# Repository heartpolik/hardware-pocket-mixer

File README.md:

# diy-mixer

Портативний 4-канальний стереомікшер для поля й столу. У репозиторії два підпроєкти:

| Тека | Що це | Стан |
|---|---|---|
| [analog-mixer/](analog-mixer/README.md) | **Rev A, аналоговий**: звук іде крізь фейдери й op-amp, ±12 V від 2S LiPo, ESP32-C3 керує ключами й метрами; дві плати | плати розведено, Gerber і BOM готові |
| [digital-mixer/](digital-mixer/README.md) | **Цифровий**, формфактор і функції на зразок TX-6: АЦП → Teensy 4.1 (мікс, EQ, ефекти) → ЦАП, USB-аудіоінтерфейс 8 каналів, MIDI, рекордер на microSD | плата 4 шари розведена (DRC 0), Gerber / BOM — далі |
| [common/](common/README.md) | спільні скрипти: схема, розстановка, трасування, footprint, 3D | — |

Правила роботи для обох — [CLAUDE.md](CLAUDE.md). Рішення кожного підпроєкту — у його
`docs/decisions.md`.

## Походження та ліцензія

Source location: <https://github.com/heartpolik/hardware-pocket-mixer>.

| Тека | Ліцензія | Чому |
|---|---|---|
| [analog-mixer/](analog-mixer/README.md#походження-та-ліцензія), [common/](common/README.md) | CERN-OHL-S-2.0+ ([LICENSE](LICENSE)) | Rev A похідний від **mixerli** (Stahl, 2023): <https://github.com/stahlnow/mixerli> |
| [digital-mixer/](digital-mixer/README.md#ліцензія) | GPL-3.0-or-later ([digital-mixer/LICENSE](digital-mixer/LICENSE)) | власна розробка, файлів mixerli немає (DM36) |

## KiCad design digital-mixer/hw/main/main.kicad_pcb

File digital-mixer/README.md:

# digital-mixer

Портативний цифровий стереомікшер з USB-аудіоінтерфейсом. Від teenage engineering TX-6 беремо
формфактор і функції (EQ, компресор, ефекти, cue, сцени, MIDI, рекордер), але не схемотехніку.

> [!NOTE]
> Стан: плата розведена ([docs/04-pcb.md](docs/04-pcb.md)), прошивка 0.2 з емулятором ([docs/06-firmware.md](docs/06-firmware.md)), схема — [docs/03-schematic.md](docs/03-schematic.md); ТЗ — [docs/01-spec.md](docs/01-spec.md), дослідження — [docs/00-research.md](docs/00-research.md). Наступний крок — макет на готових
> платах: Teensy 4.1 + PCM1865 + PCM5102A, перевірка USB-аудіо 8 каналів у Windows, macOS та iOS.

```mermaid
flowchart LR
    IN(["4 стерео входи"]) --> ADC["2 × PCM1865<br/>TDM"] --> T["Teensy 4.1<br/>мікс, EQ, компресор,<br/>2 FX-шини, метри"]
    T --> DAC["3 × PCM5102A"] --> OUT(["MAIN, AUX,<br/>навушники"])
    T <-->|"USB HS: 8 вх / 2 вих,<br/>MIDI"| PC(["DAW"])
    T --> SD[("microSD<br/>рекордер")]
    UI["Фейдери, 12 енкодерів,<br/>кнопки, дисплей 1,47″"] <--> T
```

| Документ | Зміст |
|---|---|
| [docs/00-research.md](docs/00-research.md) | TX-6, варіанти архітектури, канали й USB, живлення, функції, ризики |
| [docs/01-spec.md](docs/01-spec.md) | **ТЗ Rev 1:** функціонал, керування, роз'єми, ТТХ |
| [docs/02-components.md](docs/02-components.md) | Фейдери, енкодери, живлення 1S, монтаж Teensy, AliExpress чи JLCPCB |
| [docs/03-schematic.md](docs/03-schematic.md) | **Принципова схема** (KiCad, [PDF](hw/main/main.pdf)), виводи Teensy, макет розташування |
| [docs/04-pcb.md](docs/04-pcb.md) | **Плата:** чотиришарова 104,5 × 136,5 мм (компоновка C), Teensy на гребінках з PSRAM (DM35), розведена, DRC 0 порушень, 0 розривів |
| [docs/05-fab.md](docs/05-fab.md) | **Виготовлення:** Gerber, BOM, файли PCBA для NextPCB, [інтерактивний BOM](docs/ibom/ibom.html), порядок ручного монтажу |
| [docs/07-review.md](docs/07-review.md) | **Перевірка перед замовленням:** що знайдено й виправлено, що перевірено, що звірити; покращення до наступної версії |
| [docs/06-firmware.md](docs/06-firmware.md) | **Прошивка й емулятор:** ядро C++ ([firmware/](firmware/README.md)), емулятор на SDL2, керування, ефекти, MIDI CC, що перевірити на макеті |
| [docs/calc/](docs/calc/power.py) | Розрахунок живлення |
| [docs/decisions.md](docs/decisions.md) | Журнал рішень цифрового підпроєкту (DM1…) |
| [docs/datasheets/](docs/datasheets/README.md) | Datasheets цього підпроєкту |

З аналогового [Rev A](../analog-mixer/README.md) переносимо деталі там, де вони підходять:
USB-C GCT USB4085, захист USBLC6-2SC6, MBR0530 і AO3401A (load sharing).

## Ліцензія

SPDX-License-Identifier: GPL-3.0-or-later — повний текст у [LICENSE](LICENSE). Стосується всього в
`digital-mixer/`: схеми, плати, бібліотек, документації й прошивки (DM36).

Цифрова версія не є похідною від mixerli: файлів звідти в ній немає (джеки — PJ-327A, footprint і модель
згенеровано тут за кресленням продавця, DM38). Чужі файли зберігають свої ліцензії:
символ Teensy 4.1 від XenGi — MIT ([hw/lib/third_party](hw/lib/third_party/LICENSE-teensy_library.txt));
стандартні бібліотеки KiCad — за їхньою ліцензією з винятком для проєктів; datasheets — власність
виробників.

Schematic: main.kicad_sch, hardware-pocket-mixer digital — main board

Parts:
C1, C2, C4, C5, C6, C7, C20, C23, C32, C35, C42, C44, C53, C55, C64, C66, C82: 10u; C_1206_3216Metric
C3, C17, C19, C21, C22, C29, C31, C33, C34, C38, C39, C40, C43, C49, C50, C51, C54, C60, C61, C62, C65, C75, C76, C77, C78, C79, C80, C81: 100n; C_0805_2012Metric
C8, C9: 22u; C_1206_3216Metric
C10, C16, C28, C69, C70, C73, C74: 1u; C_0805_2012Metric
C11: 2.2u; C_1206_3216Metric
C12, C13, C14, C15, C24, C25, C26, C27: 10u 16V; CP_Elec_4x5.4
C18, C30, C41, C52, C63: 1u; C_1206_3216Metric
C36, C37, C47, C48, C58, C59, C71, C72: 2.2u; C_0805_2012Metric
C45, C46, C56, C57, C67, C68: 2.2n; C_0805_2012Metric
D1: red; LED_0805_2012Metric
D2: green; LED_0805_2012Metric
D3: MBR0530; D_SOD-123
DS1: GMT147SPI 1.47in 172x320; LCD_GMT147SPI
J1: GCT USB4110-GF-A; USB_C_Receptacle_GCT_USB4110
J2: LiPo 1S 3000 mAh (з платою захисту); JST_PH_S2B-PH-SM4-TB_1x02-1MP_P2.00mm_Horizontal
J3: IN1 PJ-327A; Jack_3.5mm_PJ-327A_SMT_Horizontal
J4: IN2 PJ-327A; Jack_3.5mm_PJ-327A_SMT_Horizontal
J5: IN3 PJ-327A; Jack_3.5mm_PJ-327A_SMT_Horizontal
J6: IN4 PJ-327A; Jack_3.5mm_PJ-327A_SMT_Horizontal
J7: MAIN OUT PJ-327A; Jack_3.5mm_PJ-327A_SMT_Horizontal
J8: AUX OUT PJ-327A; Jack_3.5mm_PJ-327A_SMT_Horizontal
J9: PHONES PJ-327A; Jack_3.5mm_PJ-327A_SMT_Horizontal
J10: MIDI OUT PJ-327A; Jack_3.5mm_PJ-327A_SMT_Horizontal
L1: 0.47u XFL4015-471ME; L_Coilcraft_XFL4015
Q1: AO3401A; SOT-23
R1, R2, R3, R4: 4.7k; R_0805_2012Metric
R5, R6, R7, R8, R9, R31, R40: 33; R_0805_2012Metric
R10, R11, R24, R26, R28, R30, R33, R35, R37, R39: 10k; R_0805_2012Metric
R12, R13, R19, R22, R23, R25, R27, R29, R32, R34, R36, R38: 100k; R_0805_2012Metric
R14, R15: 5.1k; R_0805_2012Metric
R16: 2.4k; R_0805_2012Metric
R17, R18: 1k; R_0805_2012Metric
R20: 665k; R_0805_2012Metric
R21: 91k; R_0805_2012Metric
R41, R42, R43, R44, R45, R46: 470; R_0805_2012Metric
R47: 33 0.5W; R_2010_5025Metric
R48: 10 0.25W; R_1206_3216Metric
RV1, RV2, RV3, RV4: RS201111J011 10k B; Potentiometer_Alps_RS20111_Single_Slide
SW1: Power 5.8mm DPDT self-lock SMD; SW_Push_Latching_DPDT_5.8mm_SMD
SW2: EC12SY ch1.1; RotaryEncoder_EC12SY_SMD
SW3: EC12SY ch1.2; RotaryEncoder_EC12SY_SMD
SW4: EC12SY ch1.3; RotaryEncoder_EC12SY_SMD
SW5: Mute 1 TSF-1266; SW_TSF-1266_6x6mm_SMD
SW6: EC12SY ch2.1; RotaryEncoder_EC12SY_SMD
SW7: EC12SY ch2.2; RotaryEncoder_EC12SY_SMD
SW8: EC12SY ch2.3; RotaryEncoder_EC12SY_SMD
SW9: Mute 2 TSF-1266; SW_TSF-1266_6x6mm_SMD
SW10: EC12SY ch3.1; RotaryEncoder_EC12SY_SMD
SW11: EC12SY ch3.2; RotaryEncoder_EC12SY_SMD
SW12: EC12SY ch3.3; RotaryEncoder_EC12SY_SMD
SW13: Mute 3 TSF-1266; SW_TSF-1266_6x6mm_SMD
SW14: EC12SY ch4.1; RotaryEncoder_EC12SY_SMD
SW15: EC12SY ch4.2; RotaryEncoder_EC12SY_SMD
SW16: EC12SY ch4.3; RotaryEncoder_EC12SY_SMD
SW17: Mute 4 TSF-1266; SW_TSF-1266_6x6mm_SMD
SW18: EC12SY master; RotaryEncoder_EC12SY_SMD
SW19: FX1 TSF-1266; SW_TSF-1266_6x6mm_SMD
SW20: FX2 TSF-1266; SW_TSF-1266_6x6mm_SMD
SW21: AUX TSF-1266; SW_TSF-1266_6x6mm_SMD
SW22: SHIFT TSF-1266; SW_TSF-1266_6x6mm_SMD
U1: Teensy 4.1; Teensy41_THT
U2: USBLC6-2SC6; SOT-23-6
U3: TP4056; SOIC-8-1EP_3.9x4.9mm_P1.27mm_EP2.41x3.3mm
U4: TPS63802; Texas_VSON-HR-10_2x3mm_P0.5mm
U5: LP5907MFX-3.3; SOT-23-5
U6, U7: PCM1865; TSSOP-30_4.4x7.8mm_P0.5mm
U8, U9, U10: PCM5102A; TSSOP-20_4.4x6.5mm_P0.65mm
U11: TPA6132A2; WQFN-16-1EP_3x3mm_P0.5mm_EP1.6x1.6mm
U12, U13, U14: MCP23017-E/SO; SOIC-28W_7.5x17.9mm_P1.27mm

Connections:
/+3V3: C2.1, C21.1, C22.1, C23.1, C33.1, C34.1, C35.1, C40.1, C42.1, C51.1, C53.1, C62.1, C64.1, C75.1, C76.1, C77.1, C82.1, DS1.2, R1.1, R2.1, R3.1, R4.1, R47.1, RV1.3, RV2.3, RV3.3, RV4.3, U1.15 (3V3), U1.46 (3V3), U1.51 (3V3), U6.13 (DVDD), U6.14 (IOVDD), U7.13 (DVDD), U7.14 (IOVDD), U7.25 (MS/AD), U8.20 (DVDD), U9.20 (DVDD), U10.20 (DVDD), U12.9 (V_{DD}), U12.18 (~RESET), U13.9 (V_{DD}), U13.15 (A0), U13.18 (~RESET), U14.9 (V_{DD}), U14.16 (A1), U14.18 (~RESET)
/+3V3A: C11.1, C17.1, C18.1, C29.1, C30.1, C38.1, C39.1, C41.1, C49.1, C50.1, C52.1, C60.1, C61.1, C63.1, U5.5 (OUT), U6.8 (AVDD), U7.8 (AVDD), U8.1 (CPVDD), U8.8 (AVDD), U9.1 (CPVDD), U9.8 (AVDD), U10.1 (CPVDD), U10.8 (AVDD)
/+4V2: C1.1, C8.1, C9.1, C10.1, C71.1, R20.1, U1.48 (VIN), U4.6 (VOUT), U5.1 (IN), U5.3 (EN), U11.14 (VDD)
/ADC1_DOUT: R31.1, U6.18 (DOUT)
/ADC1_IN1_L: C12.1, U6.3 (VINL1/VIN1P)
/ADC1_IN1_R: C13.1, U6.4 (VINR1/VIN2P)
/ADC1_IN2_L: C14.1, U6.1 (VINL2/VIN1M)
/ADC1_IN2_R: C15.1, U6.2 (VINR2/VIN2M)
/ADC1_LDO: C19.1, C20.1, U6.11 (LDO)
/ADC1_VREF: C16.1, U6.6 (VREF)
/ADC2_DOUT: R40.1, U7.18 (DOUT)
/ADC2_IN3_L: C24.1, U7.3 (VINL1/VIN1P)
/ADC2_IN3_R: C25.1, U7.4 (VINR1/VIN2P)
/ADC2_IN4_L: C26.1, U7.1 (VINL2/VIN1M)
/ADC2_IN4_R: C27.1, U7.2 (VINR2/VIN2M)
/ADC2_LDO: C31.1, C32.1, U7.11 (LDO)
/ADC2_VREF: C28.1, U7.6 (VREF)
/ADC_BCK: R7.2, U6.17 (BCK), U7.17 (BCK)
/ADC_BCK_T: R7.1, U1.6 (4_BCLK2)
/ADC_DOUT: R31.2, R40.2, U1.7 (5_IN2)
/ADC_LRCK: R8.2, U6.16 (LRCK), U7.16 (LRCK)
/ADC_LRCK_T: R8.1, U1.5 (3_LRCLK2)
/ADC_MCLK: R9.2, U6.15 (SCKI), U7.15 (SCKI)
/ADC_MCLK_T: R9.1, U1.25 (33_MCLK2)
/AUX_CAPM: C47.2, U9.4 (CAPM)
/AUX_CAPP: C47.1, U9.2 (CAPP)
/AUX_L: C56.1, J8.4 (T), R43.2
/AUX_LDOO: C54.1, C55.1, U9.18 (LDOO)
/AUX_OL: R43.1, U9.6 (OUTL)
/AUX_OR: R44.1, U9.7 (OUTR)
/AUX_R: C57.1, J8.3 (R), R44.2
/AUX_VNEG: C48.1, U9.5 (VNEG)
/BAT+: C5.1, J2.1, Q1.3 (D), U3.5 (BAT)
/BB_FB: R20.2, R21.1, U4.4 (FB)
/BB_L1: L1.1, U4.9 (L1)
/BB_L2: L1.2, U4.7 (L2)
/BTN_AUX: SW21.1, U14.27 (GPA6)
/BTN_FX1: SW19.1, U14.28 (GPA7)
/BTN_FX2: SW20.1, U14.7 (GPB6)
/BTN_SHIFT: SW22.1, U1.21 (29_TX7)
/CC1: J1.A5 (CC1), R14.1
/CC2: J1.B5 (CC2), R15.1
/CHG_LED_G: D2.1 (K), U3.6 (~STDBY)
/CHG_LED_GA: D2.2 (A), R18.2
/CHG_LED_R: D1.1 (K), U3.7 (~CHRG)
/CHG_LED_RA: D1.2 (A), R17.2
/CHG_PROG: R16.1, U3.2 (PROG)
/CUE_CAPM: C58.2, U10.4 (CAPM)
/CUE_CAPP: C58.1, U10.2 (CAPP)
/CUE_L: C67.1, C69.1, R45.2
/CUE_LDOO: C65.1, C66.1, U10.18 (LDOO)
/CUE_OL: R45.1, U10.6 (OUTL)
/CUE_OR: R46.1, U10.7 (OUTR)
/CUE_R: C68.1, C70.1, R46.2
/CUE_VNEG: C59.1, U10.5 (VNEG)
/DAC_AUX: U1.24 (32_OUT1B), U9.14 (DIN)
/DAC_BCK: R5.2, U8.13 (BCK), U9.13 (BCK), U10.13 (BCK)
/DAC_BCK_T: R5.1, U1.43 (21_A7_RX5_BCLK1)
/DAC_CUE: U1.11 (9_OUT1C), U10.14 (DIN)
/DAC_LRCK: R6.2, U8.15 (LRCK), U9.15 (LRCK), U10.15 (LRCK)
/DAC_LRCK_T: R6.1, U1.42 (20_A6_TX5_LRCLK1)
/DAC_MAIN: U1.9 (7_RX2_OUT1A), U8.14 (DIN)
/DAC_XSMT: R10.1, U1.28 (36_CS), U8.17 (XSMT), U9.17 (XSMT), U10.17 (XSMT)
/ENC1_1_A: SW2.A, U12.21 (GPA0)
/ENC1_1_B: SW2.B, U12.22 (GPA1)
/ENC1_1_SW: SW2.S1, U14.21 (GPA0)
/ENC1_2_A: SW3.A, U12.23 (GPA2)
/ENC1_2_B: SW3.B, U12.24 (GPA3)
/ENC1_2_SW: SW3.S1, U14.22 (GPA1)
/ENC1_3_A: SW4.A, U12.25 (GPA4)
/ENC1_3_B: SW4.B, U12.26 (GPA5)
/ENC1_3_SW: SW4.S1, U14.23 (GPA2)
/ENC2_1_A: SW6.A, U12.1 (GPB0)
/ENC2_1_B: SW6.B, U12.2 (GPB1)
/ENC2_1_SW: SW6.S1, U14.24 (GPA3)
/ENC2_2_A: SW7.A, U12.3 (GPB2)
/ENC2_2_B: SW7.B, U12.4 (GPB3)
/ENC2_2_SW: SW7.S1, U14.25 (GPA4)
/ENC2_3_A: SW8.A, U12.5 (GPB4)
/ENC2_3_B: SW8.B, U12.6 (GPB5)
/ENC2_3_SW: SW8.S1, U14.26 (GPA5)
/ENC3_1_A: SW10.A, U13.21 (GPA0)
/ENC3_1_B: SW10.B, U13.22 (GPA1)
/ENC3_1_SW: SW10.S1, U14.1 (GPB0)
/ENC3_2_A: SW11.A, U13.23 (GPA2)
/ENC3_2_B: SW11.B, U13.24 (GPA3)
/ENC3_2_SW: SW11.S1, U14.2 (GPB1)
/ENC3_3_A: SW12.A, U13.25 (GPA4)
/ENC3_3_B: SW12.B, U13.26 (GPA5)
/ENC3_3_SW: SW12.S1, U14.3 (GPB2)
/ENC4_1_A: SW14.A, U13.1 (GPB0)
/ENC4_1_B: SW14.B, U13.2 (GPB1)
/ENC4_1_SW: SW14.S1, U14.4 (GPB3)
/ENC4_2_A: SW15.A, U13.3 (GPB2)
/ENC4_2_B: SW15.B, U13.4 (GPB3)
/ENC4_2_SW: SW15.S1, U14.5 (GPB4)
/ENC4_3_A: SW16.A, U13.5 (GPB4)
/ENC4_3_B: SW16.B, U13.6 (GPB5)
/ENC4_3_SW: SW16.S1, U14.6 (GPB5)
/ENC_M_A: SW18.A, U1.2 (0_RX1_CRX2_CS1)
/ENC_M_B: SW18.B, U1.3 (1_TX1_CTX2_MISO1)
/ENC_M_SW: SW18.S1, U1.4 (2_OUT2)
/FADER1: C78.1, RV1.2, U1.36 (14_A0_TX3_SPDIF_OUT)
/FADER2: C79.1, RV2.2, U1.37 (15_A1_RX3_SPDIF_IN)
/FADER3: C80.1, RV3.2, U1.38 (16_A2_RX4_SCL1)
/FADER4: C81.1, RV4.2, U1.39 (17_A3_TX4_SDA1)
/GND: C1.2, C2.2, C3.2, C4.2, C5.2, C6.2, C7.2, C8.2, C9.2, C10.2, C11.2, C16.2, C17.2, C18.2, C19.2, C20.2, C21.2, C22.2, C23.2, C28.2, C29.2, C30.2, C31.2, C32.2, C33.2, C34.2, C35.2, C37.2, C38.2, C39.2, C40.2, C41.2, C42.2, C43.2, C44.2, C45.2, C46.2, C48.2, C49.2, C50.2, C51.2, C52.2, C53.2, C54.2, C55.2, C56.2, C57.2, C59.2, C60.2, C61.2, C62.2, C63.2, C64.2, C65.2, C66.2, C67.2, C68.2, C71.2, C72.2, C73.2, C75.2, C76.2, C77.2, C78.2, C79.2, C80.2, C81.2, C82.2, DS1.1, J1.A1 (GND), J1.A12 (GND), J1.B1 (GND), J1.B12 (GND), J1.SH (SHIELD), J2.2, J2.MP (MountPin), J3.1 (S), J3.2 (S2), J4.1 (S), J4.2 (S2), J5.1 (S), J5.2 (S2), J6.1 (S), J6.2 (S2), J7.1 (S), J7.2 (S2), J8.1 (S), J8.2 (S2), J9.1 (S), J9.2 (S2), J10.1 (S), J10.2 (S2), R10.2, R11.2, R13.2, R14.2, R15.2, R16.2, R19.2, R21.2, R22.2, R23.2, R25.2, R27.2, R29.2, R32.2, R34.2, R36.2, R38.2, RV1.1, RV2.1, RV3.1, RV4.1, SW1.1 (A), SW2.C, SW2.MP, SW2.S2, SW3.C, SW3.MP, SW3.S2, SW4.C, SW4.MP, SW4.S2, SW5.2, SW6.C, SW6.MP, SW6.S2, SW7.C, SW7.MP, SW7.S2, SW8.C, SW8.MP, SW8.S2, SW9.2, SW10.C, SW10.MP, SW10.S2, SW11.C, SW11.MP, SW11.S2, SW12.C, SW12.MP, SW12.S2, SW13.2, SW14.C, SW14.MP, SW14.S2, SW15.C, SW15.MP, SW15.S2, SW16.C, SW16.MP, SW16.S2, SW17.2, SW18.C, SW18.MP, SW18.S2, SW19.2, SW20.2, SW21.2, SW22.2, U1.1 (GND), U1.34 (GND), U1.47 (GND), U1.52 (GND), U2.2 (GND), U3.1 (TEMP), U3.3 (GND), U3.9 (EPAD), U4.2 (MODE), U4.3 (AGND), U4.8 (GND), U5.2 (GND), U6.7 (AGND), U6.10 (XI), U6.12 (DGND), U6.25 (MS/AD), U6.26 (MD0), U7.7 (AGND), U7.10 (XI), U7.12 (DGND), U7.26 (MD0), U8.3 (CPGND), U8.9 (AGND), U8.10 (DEMP), U8.11 (FLT), U8.12 (SCK), U8.16 (FMT), U8.19 (DGND), U9.3 (CPGND), U9.9 (AGND), U9.10 (DEMP), U9.11 (FLT), U9.12 (SCK), U9.16 (FMT), U9.19 (DGND), U10.3 (CPGND), U10.9 (AGND), U10.10 (DEMP), U10.11 (FLT), U10.12 (SCK), U10.16 (FMT), U10.19 (DGND), U11.2 (INL+), U11.3 (INR+), U11.6 (G0), U11.7 (G1), U11.10 (PGND), U11.15 (SGND), U11.17 (EP), U12.10 (V_{SS}), U12.15 (A0), U12.16 (A1), U12.17 (A2), U13.10 (V_{SS}), U13.16 (A1), U13.17 (A2), U14.10 (V_{SS}), U14.15 (A0), U14.17 (A2); also elsewhere on the board
/HP_CPN: C74.2, U11.9 (CPN)
/HP_CPP: C74.1, U11.11 (CPP)
/HP_EN: R11.1, U1.29 (37_CS), U11.13 (EN)
/HP_HPVDD: C72.1, U11.12 (HPVDD)
/HP_HPVSS: C73.1, U11.8 (HPVSS)
/HP_INL: C69.2, U11.1 (INL-)
/HP_INR: C70.2, U11.4 (INR-)
/I2C2_SCL: R4.2, U1.16 (24_A10_TX6_SCL2), U12.12 (SCK), U13.12 (SCK), U14.12 (SCK)
/I2C2_SDA: R3.2, U1.17 (25_A11_RX6_SDA2), U12.13 (SDA), U13.13 (SDA), U14.13 (SDA)
/I2C_SCL: R2.2, U1.41 (19_A5_SCL), U6.24 (MC/SCL), U7.24 (MC/SCL)
/I2C_SDA: R1.2, U1.40 (18_A4_SDA), U6.23 (MOSI/SDA), U7.23 (MOSI/SDA)
/IN1_LS: C12.2, R24.2
/IN1_R: J3.3 (R), R25.1, R26.1
/IN1_RS: C13.2, R26.2
/IN1_T: J3.4 (T), R23.1, R24.1
/IN2_LS: C14.2, R28.2
/IN2_R: J4.3 (R), R29.1, R30.1
/IN2_RS: C15.2, R30.2
/IN2_T: J4.4 (T), R27.1, R28.1
/IN3_LS: C24.2, R33.2
/IN3_R: J5.3 (R), R34.1, R35.1
/IN3_RS: C25.2, R35.2
/IN3_T: J5.4 (T), R32.1, R33.1
/IN4_LS: C26.2, R37.2
/IN4_R: J6.3 (R), R38.1, R39.1
/IN4_RS: C27.2, R39.2
/IN4_T: J6.4 (T), R36.1, R37.1
/LCD_BLK: DS1.8, U1.20 (28_RX7)
/LCD_CS: DS1.7, U1.12 (10_CS_MQSR)
/LCD_DC: DS1.6, U1.32 (40_A16)
/LCD_MOSI: DS1.4, U1.13 (11_MOSI_CTX1)
/LCD_RES: DS1.5, U1.33 (41_A17)
/LCD_SCK: DS1.3, U1.35 (13_SCK_LED)
/MAIN_CAPM: C36.2, U8.4 (CAPM)
/MAIN_CAPP: C36.1, U8.2 (CAPP)
/MAIN_L: C45.1, J7.4 (T), R41.2
/MAIN_LDOO: C43.1, C44.1, U8.18 (LDOO)
/MAIN_OL: R41.1, U8.6 (OUTL)
/MAIN_OR: R42.1, U8.7 (OUTR)
/MAIN_R: C46.1, J7.3 (R), R42.2
/MAIN_VNEG: C37.1, U8.5 (VNEG)
/MCP1_INT: U1.22 (30_CRX3), U12.20 (INTA)
/MCP2_INT: U1.23 (31_CTX3), U13.20 (INTA)
/MCP3_INT: U1.44 (22_A8_CTX1), U14.20 (INTA)
/MIDI_SINK: J10.4 (T), R48.2
/MIDI_SRC: J10.3 (R), R47.2
/MIDI_TX: R48.1, U1.27 (35_TX8)
/MUTE1: SW5.1, U12.27 (GPA6)
/MUTE2: SW9.1, U12.7 (GPB6)
/MUTE3: SW13.1, U13.27 (GPA6)
/MUTE4: SW17.1, U13.7 (GPB6)
/PH_L: J9.4 (T), U11.16 (OUTL)
/PH_R: J9.3 (R), U11.5 (OUTR)
/PWR_EN: R22.1, SW1.2 (B), U4.1 (EN)
/USB_C_DN: J1.A7 (D-), J1.B7 (D-), U2.3 (I/O2)
/USB_C_DP: J1.A6 (D+), J1.B6 (D+), U2.1 (I/O1)
/USB_DN: U1.66 (D-), U2.4 (I/O2)
/USB_DP: U1.67 (D+), U2.6 (I/O1)
/VBAT_SENSE: C3.1, R12.2, R13.1, U1.30 (38_CS1_IN1)
/VBUS: C4.1, D3.2 (A), J1.A4 (VBUS), J1.A9 (VBUS), J1.B4 (VBUS), J1.B9 (VBUS), Q1.1 (G), R17.1, R18.1, R19.1, U1.49 (VUSB), U2.5 (VBUS), U3.4 (V_{CC}), U3.8 (CE)
/VSYS: C6.1, C7.1, D3.1 (K), Q1.2 (S), R12.1, SW1.3 (C), U4.10 (VIN)

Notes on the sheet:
Teensy 4.1 (DM4, DM12, DM35): на гребінках 2 × 24 крізь плату, зазор 2,5 мм під PSRAM; VIN = +4V2; перемичку VIN–VUSB на модулі РОЗРІЗАТИ, VUSB = VBUS з USB-C; USB device D−/D+ — отвори знизу модуля (креслення PJRC) → площадки 66/67 під ними, VUSB — дротик (49)
USB-C (GCT USB4110-GF-A, повністю SMD — під MASTER, DM25): аудіо, MIDI, заряд. CC 5,1k — пристрій-споживач; ESD USBLC6
Заряд 1S (DM11): TP4056, R_PROG 2,4k → 0,5 A; TEMP на GND — без NTC. CHRG / STDBY — світлодіоди
Load sharing (02, п. 4): від USB — через діод, акумулятор відключає P-MOSFET (затвор = VBUS)
Buck-boost TPS63802 → +4V2 (DM11). R1/R2 = 665k/91k → 4,15 V (VFB 0,5 V, табл. 10-5); L 0,47 µH XFL4015; C 10 µF вх., 2×22 µF вих. (>3,6 V). Вимикач — кнопка з фіксацією 5,8 мм на EN (DM27)
LP5907 3,3 V — аналог кодеків (+3V3A): < 6,5 µVrms, 250 mA; навантаження 128 mA (calc/power.py). Ємність на всій шині +3V3A — 0,7…10 µF (datasheet, COUT): 2,2 µF тут + 1 µF біля кожного кодека + 100 nF ≈ 8 µF
АЦП1 PCM1865 (I²C 0x94): входи IN1, IN2. Ведений TDM, слоти 1–4. Вхід: 10k послідовно (−6 dB з 10 kΩ входу) + 10 µF
АЦП2 PCM1865 (I²C 0x96): входи IN3, IN4. Ведений TDM, слоти 5–8. Вхід: 10k послідовно (−6 dB з 10 kΩ входу) + 10 µF
ЦАП MAIN PCM5102A: I²S, BCK PLL (SCK = GND), FMT/FLT/DEMP = GND; вихід 470 Ω + 2,2 nF (рис. 33). XSMT — спільний з Teensy
ЦАП AUX PCM5102A: I²S, BCK PLL (SCK = GND), FMT/FLT/DEMP = GND; вихід 470 Ω + 2,2 nF (рис. 33). XSMT — спільний з Teensy
ЦАП CUE PCM5102A: I²S, BCK PLL (SCK = GND), FMT/FLT/DEMP = GND; вихід 470 Ω + 2,2 nF (рис. 33). XSMT — спільний з Teensy
Навушники TPA6132A2 (рис. 27, несиметричний вхід): G0 = G1 = GND → −6 dB (2,1 Vrms ЦАП → ≈1 Vrms); EN від Teensy. QFN — лише при передзбиранні JLCPCB (DM7)
MIDI OUT, TRS Type A (DM20): кінчик = DIN 5 (через RC 10 Ω від UART), кільце = DIN 4 (RA 33 Ω від +3,3 V), гільза = DIN 2 / GND. Значення для 3,3 V — MIDI 1.0 Electrical Spec Update, рис. 1
MCP23017 #1 (I²C2, 0x20): енкодери каналів 1, 2 (A/B), Mute; GPx7 вільні; внутрішні підтяжки 100k, INTA/INTB дзеркальні → один INT
MCP23017 #2 (I²C2, 0x21): енкодери каналів 3, 4 (A/B), Mute; GPx7 вільні; внутрішні підтяжки 100k, INTA/INTB дзеркальні → один INT
MCP23017 #3 (I²C2, 0x22): кнопки 12 енкодерів каналів (DM28: натискання — фільтр / компресор, скидання значення) і кнопки AUX, FX I, FX II (GPA6, GPA7, GPB6) — найближчий до правої колонки; GPB7 вільний
Канал 1: 3 енкодери EC12SY SMD з кнопкою (шари EQ / посили / канал, DM6, DM26), фейдер 35 мм Alps RS201111J011 (DM8, DM39), Mute — тактова кнопка TSF-1266 (DM16)
Канал 2: 3 енкодери EC12SY SMD з кнопкою (шари EQ / посили / канал, DM6, DM26), фейдер 35 мм Alps RS201111J011 (DM8, DM39), Mute — тактова кнопка TSF-1266 (DM16)
Канал 3: 3 енкодери EC12SY SMD з кнопкою (шари EQ / посили / канал, DM6, DM26), фейдер 35 мм Alps RS201111J011 (DM8, DM39), Mute — тактова кнопка TSF-1266 (DM16)
Канал 4: 3 енкодери EC12SY SMD з кнопкою (шари EQ / посили / канал, DM6, DM26), фейдер 35 мм Alps RS201111J011 (DM8, DM39), Mute — тактова кнопка TSF-1266 (DM16)
Майстер: енкодер EC12SY з кнопкою, кнопки AUX, FX I, FX II, SHIFT (TSF-1266; CUE = SHIFT + Mute, DM28); дисплей GMT147SPI 1,47" 172×320 ST7789P3, SPI, на гребінці (DM18, DM23); виводи — за кресленням продавця
Прапорці живлення: шини, які в символах не мають «виходу живлення» (GND, вихід 3,3 V Teensy, VBUS, внутрішні LDO PCM1865, накачка TPA6132A2, VSYS після діода / ключа)

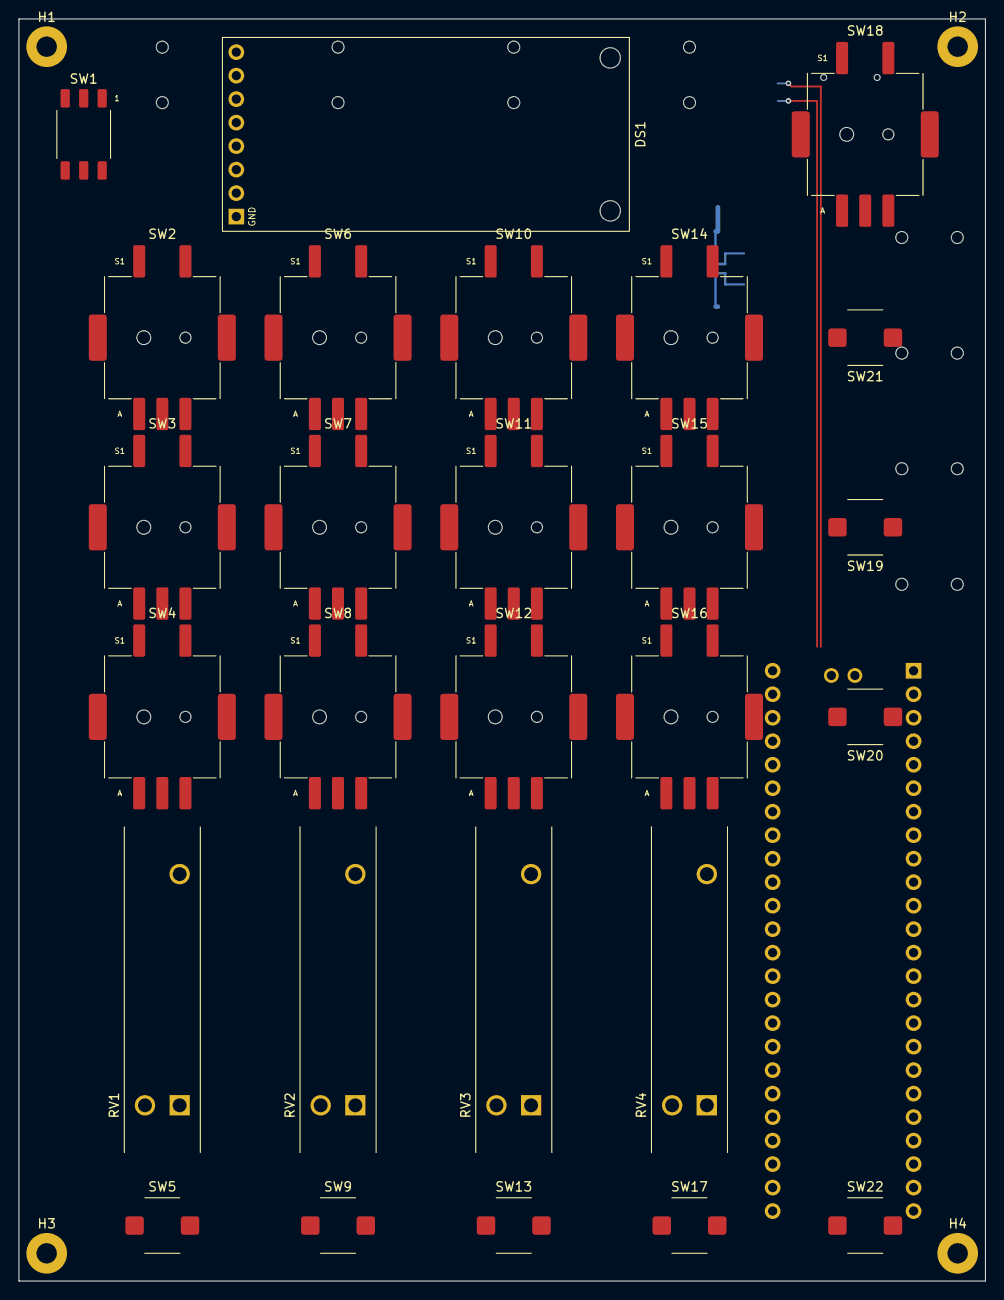
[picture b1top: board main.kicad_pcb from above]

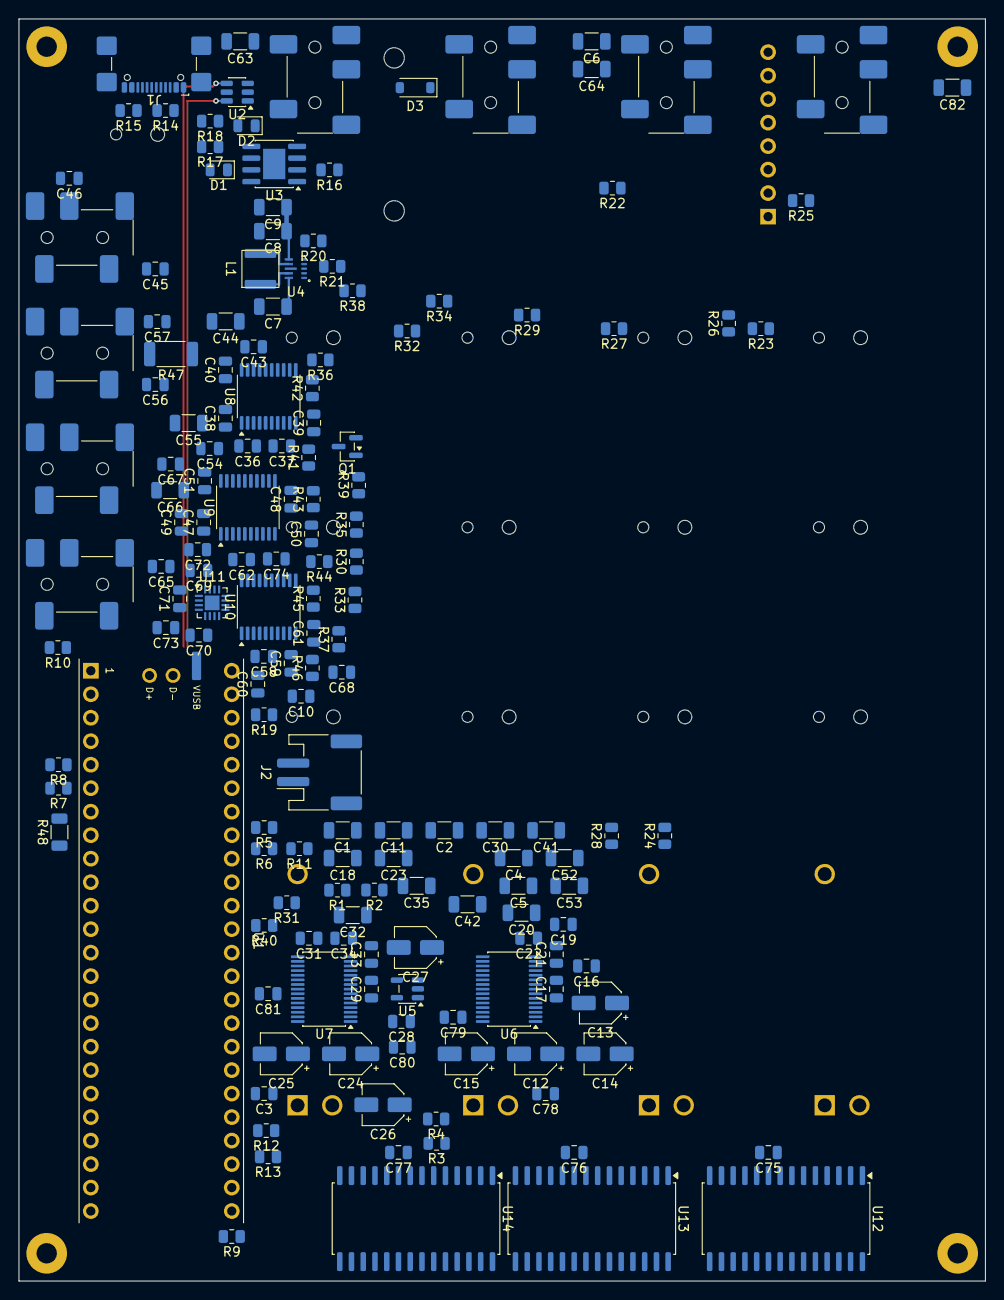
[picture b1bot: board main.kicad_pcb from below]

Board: 2 copper layers, 104.5 x 136.5 mm, 190 parts (159 on the bottom side), 168 nets.

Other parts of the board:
H1, H2, H3, H4: M2; MountingHole_2.2mm_M2_Pad_Standoff_2Side

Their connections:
/GND: H1.1, H2.1, H3.1, H4.1; also elsewhere on the board

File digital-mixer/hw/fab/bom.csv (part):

К-сть,Номінал,Footprint,Виробник,Партномер,Опис,Монтаж,Позначення
17,10u,Capacitor_SMD:C_1206_3216Metric,Samsung,CL31B106KAHNNNE,MLCC 10 uF 25 V X7R 1206,NextPCB,"C1,C2,C4,C5,C6,C7,C20,C23,C32,C35,C42,C44,C53,C55,C64,C66,C82"
28,100n,Capacitor_SMD:C_0805_2012Metric,Samsung,CL21B104KBCNNNC,MLCC 100 nF 50 V X7R 0805,NextPCB,"C3,C17,C19,C21,C22,C29,C31,C33,C34,C38,C39,C40,C43,C49,C50,C51,C54,C60,C61,C62,C65,C75,C76,C77,C78,C79,C80,C81"
2,22u,Capacitor_SMD:C_1206_3216Metric,Samsung,CL31A226KAHNNNE,MLCC 22 uF 25 V X5R 1206,NextPCB,"C8,C9"
7,1u,Capacitor_SMD:C_0805_2012Metric,Samsung,CL21B105KAFNNNE,MLCC 1 uF 25 V X7R 0805,NextPCB,"C10,C16,C28,C69,C70,C73,C74"
1,2.2u,Capacitor_SMD:C_1206_3216Metric,Samsung,CL31B225KBHNNNE,MLCC 2.2 uF 50 V X7R 1206,NextPCB,C11
8,10u 16V,Capacitor_SMD:CP_Elec_4x5.4,Panasonic,EEE-1CA100SR,Al electrolytic 10 uF 16 V 4x5.4 SMD,NextPCB,"C12,C13,C14,C15,C24,C25,C26,C27"
5,1u,Capacitor_SMD:C_1206_3216Metric,Samsung,CL31B105KBHNNNE,MLCC 1 uF 50 V X7R 1206,NextPCB,"C18,C30,C41,C52,C63"
8,2.2u,Capacitor_SMD:C_0805_2012Metric,Samsung,CL21B225KAFNNNE,MLCC 2.2 uF 25 V X7R 0805,NextPCB,"C36,C37,C47,C48,C58,C59,C71,C72"
6,2.2n,Capacitor_SMD:C_0805_2012Metric,Samsung,CL21C222JBFNNNE,MLCC 2.2 nF 50 V C0G 0805,NextPCB,"C45,C46,C56,C57,C67,C68"
1,red,LED_SMD:LED_0805_2012Metric,Lite-On,LTST-C171KRKT,LED red 0805,NextPCB,D1
1,green,LED_SMD:LED_0805_2012Metric,Lite-On,LTST-C171KGKT,LED green 0805,NextPCB,D2
1,MBR0530,Diode_SMD:D_SOD-123,JSCJ,MBR0530,"Schottky 30 V 0.5 A, SOD-123",NextPCB,D3
1,GMT147SPI 1.47in 172x320,pocket-digital:LCD_GMT147SPI,,,,"вручну: THT, гребінка дисплея",DS1
1,GCT USB4110-GF-A,Connector_USB:USB_C_Receptacle_GCT_USB4110,GCT,USB4110-GF-A,"USB-C 2.0 receptacle, SMT",NextPCB,J1
1,LiPo 1S 3000 mAh (з платою захисту),Connector_JST:JST_PH_S2B-PH-SM4-TB_1x02-1MP_P2.00mm_Horizontal,JST,S2B-PH-SM4-TB(LF)(SN),"PH 2-pin side entry, SMT",NextPCB,J2
1,IN1 PJ-327A,pocket-digital:Jack_3.5mm_PJ-327A_SMT_Horizontal,(AliExpress seller),PJ-327A,"3.5 mm stereo jack SMT, 5 legs (DM38)",вручну: PJ-327A з AliExpress за кресленням продавця (DM38) - в інших виробників інші лапки,J3
1,IN2 PJ-327A,pocket-digital:Jack_3.5mm_PJ-327A_SMT_Horizontal,(AliExpress seller),PJ-327A,"3.5 mm stereo jack SMT, 5 legs (DM38)",вручну: PJ-327A з AliExpress за кресленням продавця (DM38) - в інших виробників інші лапки,J4
1,IN3 PJ-327A,pocket-digital:Jack_3.5mm_PJ-327A_SMT_Horizontal,(AliExpress seller),PJ-327A,"3.5 mm stereo jack SMT, 5 legs (DM38)",вручну: PJ-327A з AliExpress за кресленням продавця (DM38) - в інших виробників інші лапки,J5
1,IN4 PJ-327A,pocket-digital:Jack_3.5mm_PJ-327A_SMT_Horizontal,(AliExpress seller),PJ-327A,"3.5 mm stereo jack SMT, 5 legs (DM38)",вручну: PJ-327A з AliExpress за кресленням продавця (DM38) - в інших виробників інші лапки,J6
1,MAIN OUT PJ-327A,pocket-digital:Jack_3.5mm_PJ-327A_SMT_Horizontal,(AliExpress seller),PJ-327A,"3.5 mm stereo jack SMT, 5 legs (DM38)",вручну: PJ-327A з AliExpress за кресленням продавця (DM38) - в інших виробників інші лапки,J7
1,AUX OUT PJ-327A,pocket-digital:Jack_3.5mm_PJ-327A_SMT_Horizontal,(AliExpress seller),PJ-327A,"3.5 mm stereo jack SMT, 5 legs (DM38)",вручну: PJ-327A з AliExpress за кресленням продавця (DM38) - в інших виробників інші лапки,J8
1,PHONES PJ-327A,pocket-digital:Jack_3.5mm_PJ-327A_SMT_Horizontal,(AliExpress seller),PJ-327A,"3.5 mm stereo jack SMT, 5 legs (DM38)",вручну: PJ-327A з AliExpress за кресленням продавця (DM38) - в інших виробників інші лапки,J9
1,MIDI OUT PJ-327A,pocket-digital:Jack_3.5mm_PJ-327A_SMT_Horizontal,(AliExpress seller),PJ-327A,"3.5 mm stereo jack SMT, 5 legs (DM38)",вручну: PJ-327A з AliExpress за кресленням продавця (DM38) - в інших виробників інші лапки,J10
1,0.47u XFL4015-471ME,pocket-digital:L_Coilcraft_XFL4015,Coilcraft,XFL4015-471MEC,"inductor 0.47 uH 6.6 A, 4x4x1.5",NextPCB,L1
1,AO3401A,Package_TO_SOT_SMD:SOT-23,Alpha & Omega,AO3401A,"P-MOSFET 30 V 4 A, SOT-23",NextPCB,Q1
4,4.7k,Resistor_SMD:R_0805_2012Metric,Yageo,RC0805FR-074K7L,resistor 4.7 k 1% 0805,NextPCB,"R1,R2,R3,R4"
7,33,Resistor_SMD:R_0805_2012Metric,Yageo,RC0805FR-0733RL,resistor 33 R 1% 0805,NextPCB,"R5,R6,R7,R8,R9,R31,R40"
10,10k,Resistor_SMD:R_0805_2012Metric,Yageo,RC0805FR-0710KL,resistor 10 k 1% 0805,NextPCB,"R10,R11,R24,R26,R28,R30,R33,R35,R37,R39"
12,100k,Resistor_SMD:R_0805_2012Metric,Yageo,RC0805FR-07100KL,resistor 100 k 1% 0805,NextPCB,"R12,R13,R19,R22,R23,R25,R27,R29,R32,R34,R36,R38"
2,5.1k,Resistor_SMD:R_0805_2012Metric,Yageo,RC0805FR-075K1L,resistor 5.1 k 1% 0805,NextPCB,"R14,R15"
1,2.4k,Resistor_SMD:R_0805_2012Metric,Yageo,RC0805FR-072K4L,resistor 2.4 k 1% 0805,NextPCB,R16
2,1k,Resistor_SMD:R_0805_2012Metric,Yageo,RC0805FR-071KL,resistor 1 k 1% 0805,NextPCB,"R17,R18"
1,665k,Resistor_SMD:R_0805_2012Metric,Yageo,RC0805FR-07665KL,resistor 665 k 1% 0805 - ПЕРЕВІРИТИ part number,NextPCB,R20
1,91k,Resistor_SMD:R_0805_2012Metric,Yageo,RC0805FR-0791KL,resistor 91 k 1% 0805,NextPCB,R21
6,470,Resistor_SMD:R_0805_2012Metric,Yageo,RC0805FR-07470RL,resistor 470 R 1% 0805,NextPCB,"R41,R42,R43,R44,R45,R46"
1,33 0.5W,Resistor_SMD:R_2010_5025Metric,Yageo,RC2010FK-0733RL,resistor 33 R 1% 0.75 W 2010,NextPCB,R47
1,10 0.25W,Resistor_SMD:R_1206_3216Metric,Yageo,RC1206FR-0710RL,resistor 10 R 1% 0.5 W 1206,NextPCB,R48
4,RS201111J011 10k B,pocket-digital:Potentiometer_Alps_RS20111_Single_Slide,,,,"вручну: THT, фейдер Alps RS201111J011 (AliExpress, DM39)","RV1,RV2,RV3,RV4"
1,Power 5.8mm DPDT self-lock SMD,pocket-digital:SW_Push_Latching_DPDT_5.8mm_SMD,,,,"вручну: верхній бік, AliExpress (DM27)",SW1
1,EC12SY ch1.1,pocket-digital:RotaryEncoder_EC12SY_SMD,,,,"вручну: верхній бік, AliExpress (DM26)",SW2
1,EC12SY ch1.2,pocket-digital:RotaryEncoder_EC12SY_SMD,,,,"вручну: верхній бік, AliExpress (DM26)",SW3
1,EC12SY ch1.3,pocket-digital:RotaryEncoder_EC12SY_SMD,,,,"вручну: верхній бік, AliExpress (DM26)",SW4
1,Mute 1 TSF-1266,pocket-digital:SW_TSF-1266_6x6mm_SMD,,,,"вручну: верхній бік, AliExpress",SW5
1,EC12SY ch2.1,pocket-digital:RotaryEncoder_EC12SY_SMD,,,,"вручну: верхній бік, AliExpress (DM26)",SW6
1,EC12SY ch2.2,pocket-digital:RotaryEncoder_EC12SY_SMD,,,,"вручну: верхній бік, AliExpress (DM26)",SW7
1,EC12SY ch2.3,pocket-digital:RotaryEncoder_EC12SY_SMD,,,,"вручну: верхній бік, AliExpress (DM26)",SW8
1,Mute 2 TSF-1266,pocket-digital:SW_TSF-1266_6x6mm_SMD,,,,"вручну: верхній бік, AliExpress",SW9
1,EC12SY ch3.1,pocket-digital:RotaryEncoder_EC12SY_SMD,,,,"вручну: верхній бік, AliExpress (DM26)",SW10
1,EC12SY ch3.2,pocket-digital:RotaryEncoder_EC12SY_SMD,,,,"вручну: верхній бік, AliExpress (DM26)",SW11
1,EC12SY ch3.3,pocket-digital:RotaryEncoder_EC12SY_SMD,,,,"вручну: верхній бік, AliExpress (DM26)",SW12
1,Mute 3 TSF-1266,pocket-digital:SW_TSF-1266_6x6mm_SMD,,,,"вручну: верхній бік, AliExpress",SW13
1,EC12SY ch4.1,pocket-digital:RotaryEncoder_EC12SY_SMD,,,,"вручну: верхній бік, AliExpress (DM26)",SW14
1,EC12SY ch4.2,pocket-digital:RotaryEncoder_EC12SY_SMD,,,,"вручну: верхній бік, AliExpress (DM26)",SW15
1,EC12SY ch4.3,pocket-digital:RotaryEncoder_EC12SY_SMD,,,,"вручну: верхній бік, AliExpress (DM26)",SW16
1,Mute 4 TSF-1266,pocket-digital:SW_TSF-1266_6x6mm_SMD,,,,"вручну: верхній бік, AliExpress",SW17
1,EC12SY master,pocket-digital:RotaryEncoder_EC12SY_SMD,,,,"вручну: верхній бік, AliExpress (DM26)",SW18
1,FX1 TSF-1266,pocket-digital:SW_TSF-1266_6x6mm_SMD,,,,"вручну: верхній бік, AliExpress",SW19
1,FX2 TSF-1266,pocket-digital:SW_TSF-1266_6x6mm_SMD,,,,"вручну: верхній бік, AliExpress",SW20
1,AUX TSF-1266,pocket-digital:SW_TSF-1266_6x6mm_SMD,,,,"вручну: верхній бік, AliExpress",SW21
1,SHIFT TSF-1266,pocket-digital:SW_TSF-1266_6x6mm_SMD,,,,"вручну: верхній бік, AliExpress",SW22
1,Teensy 4.1,pocket-digital:Teensy41_THT,,,,"вручну: Teensy 4.1 на гребінках 2 × 24 (DM35) + 3 дроти USB, PSRAM на ньому — до встановлення; після перевірки живлення",U1
1,USBLC6-2SC6,Package_TO_SOT_SMD:SOT-23-6,STMicroelectronics,USBLC6-2SC6,"USB ESD protection, SOT-23-6",NextPCB,U2
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
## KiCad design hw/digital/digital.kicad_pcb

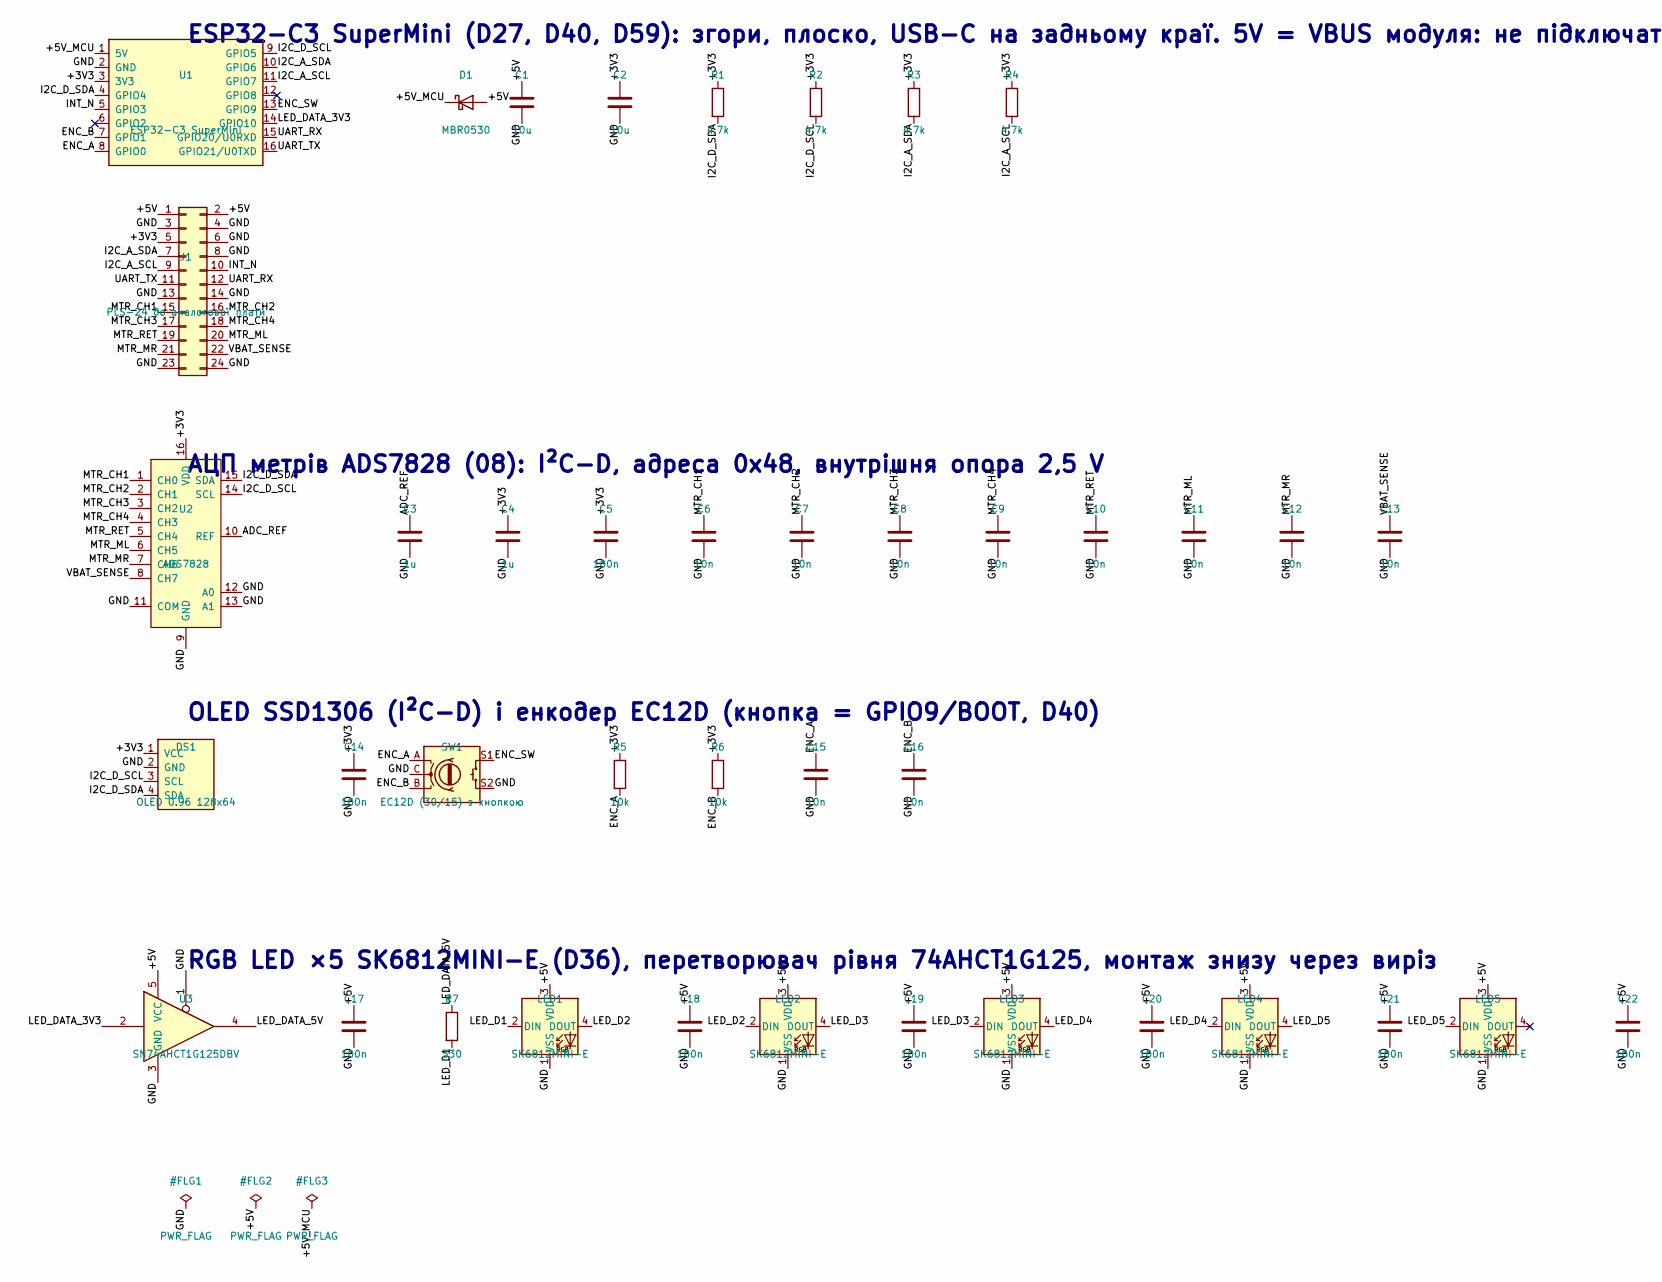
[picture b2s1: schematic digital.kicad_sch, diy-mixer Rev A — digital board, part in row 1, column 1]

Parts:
C1, C2: 10u; C_1206_3216Metric
C3, C4: 1u; C_0805_2012Metric
C5, C14, C17, C18, C19, C20, C21, C22: 100n; C_0805_2012Metric
C6, C7, C8, C9, C10, C11, C12, C13, C15, C16: 10n; C_0805_2012Metric
C23: 47u; C_1206_3216Metric
D1: MBR0530; D_SOD-123
DS1: OLED 0.96 128x64; OLED_0.96in_128x64_I2C_4pin
J1: PLS-24 до аналогової плати; PinHeader_2x12_P2.54mm_Vertical
LED1, LED2, LED3, LED4, LED5: SK6812MINI-E; LED_SK6812MINI-E_3.2x2.8mm_P1.5mm_ReverseMount
R1, R2, R3, R4: 4.7k; R_0805_2012Metric
R5, R6: 10k; R_0805_2012Metric
R7: 330; R_0805_2012Metric
SW1: EC12D (30/15) з кнопкою; Alps_EC12D_Switch
U1: ESP32-C3 SuperMini; ESP32-C3_SuperMini_SMD
U2: ADS7828; TSSOP-16_4.4x5mm_P0.65mm
U3: SN74AHCT1G125DBV; SOT-23-5

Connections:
/+3V3: C2.1, C4.1, C5.1, C14.1, DS1.1 (VCC), J1.5, R1.1, R2.1, R3.1, R4.1, R5.1, R6.1, U1.3 (3V3), U2.16 (VDD)
/+5V: C1.1, C17.1, C18.1, C19.1, C20.1, C21.1, C22.1, C23.1, D1.2 (A), J1.1, J1.2, LED1.3 (VDD), LED2.3 (VDD), LED3.3 (VDD), LED4.3 (VDD), LED5.3 (VDD), U3.5 (VCC)
/+5V_MCU: D1.1 (K), U1.1 (5V)
/ADC_REF: C3.1, U2.10 (REF)
/ENC_A: C15.1, R5.2, SW1.A, U1.8 (GPIO0)
/ENC_B: C16.1, R6.2, SW1.B, U1.7 (GPIO1)
/ENC_SW: SW1.S1, U1.13 (GPIO9)
/GND: C1.2, C2.2, C3.2, C4.2, C5.2, C6.2, C7.2, C8.2, C9.2, C10.2, C11.2, C12.2, C13.2, C14.2, C15.2, C16.2, C17.2, C18.2, C19.2, C20.2, C21.2, C22.2, C23.2, DS1.2 (GND), J1.3, J1.4, J1.6, J1.8, J1.13, J1.14, J1.23, J1.24, LED1.1 (VSS), LED2.1 (VSS), LED3.1 (VSS), LED4.1 (VSS), LED5.1 (VSS), SW1.C, SW1.S2, U1.2 (GND), U2.9 (GND), U2.11 (COM), U2.12 (A0), U2.13 (A1), U3.1, U3.3 (GND); also elsewhere on the board
/I2C_A_SCL: J1.9, R4.2, U1.11 (GPIO7)
/I2C_A_SDA: J1.7, R3.2, U1.10 (GPIO6)
/I2C_D_SCL: DS1.3 (SCL), R2.2, U1.9 (GPIO5), U2.14 (SCL)
/I2C_D_SDA: DS1.4 (SDA), R1.2, U1.4 (GPIO4), U2.15 (SDA)
/INT_N: J1.10, U1.5 (GPIO3)
/LED_D1: LED1.2 (DIN), R7.2
/LED_D2: LED1.4 (DOUT), LED2.2 (DIN)
/LED_D3: LED2.4 (DOUT), LED3.2 (DIN)
/LED_D4: LED3.4 (DOUT), LED4.2 (DIN)
/LED_D5: LED4.4 (DOUT), LED5.2 (DIN)
/LED_DATA_3V3: U1.14 (GPIO10), U3.2
/LED_DATA_5V: R7.1, U3.4
/MTR_CH1: C6.1, J1.15, U2.1 (CH0)
/MTR_CH2: C7.1, J1.16, U2.2 (CH1)
/MTR_CH3: C8.1, J1.17, U2.3 (CH2)
/MTR_CH4: C9.1, J1.18, U2.4 (CH3)
/MTR_ML: C11.1, J1.20, U2.6 (CH5)
/MTR_MR: C12.1, J1.21, U2.7 (CH6)
/MTR_RET: C10.1, J1.19, U2.5 (CH4)
/UART_RX: J1.12, U1.15 (GPIO20/U0RXD)
/UART_TX: J1.11, U1.16 (GPIO21/U0TXD)
/VBAT_SENSE: C13.1, J1.22, U2.8 (CH7)

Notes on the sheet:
ESP32-C3 SuperMini (D27, D40, D59): згори, плоско, USB-C на задньому краї. 5V = VBUS модуля: не підключати USB модуля при увімкненому мікшері
АЦП метрів ADS7828 (08): I²C-D, адреса 0x48, внутрішня опора 2,5 V
OLED SSD1306 (I²C-D) і енкодер EC12D (кнопка = GPIO9/BOOT, D40)
RGB LED ×5 SK6812MINI-E (D36), перетворювач рівня 74AHCT1G125, монтаж знизу через виріз

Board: 2 copper layers, 44 parts (39 on the bottom side), 30 nets, no tracks yet.

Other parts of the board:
H1, H2: M2; MountingHole_2.2mm_M2_Pad_Standoff_2Side

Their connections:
/GND: H1.1, H2.1; also elsewhere on the board

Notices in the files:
analog-mixer/hw/analog/analog_routed.kicad_pcb:
hardware-pocket-mixer Rev A  CERN-OHL-S-2.0+
